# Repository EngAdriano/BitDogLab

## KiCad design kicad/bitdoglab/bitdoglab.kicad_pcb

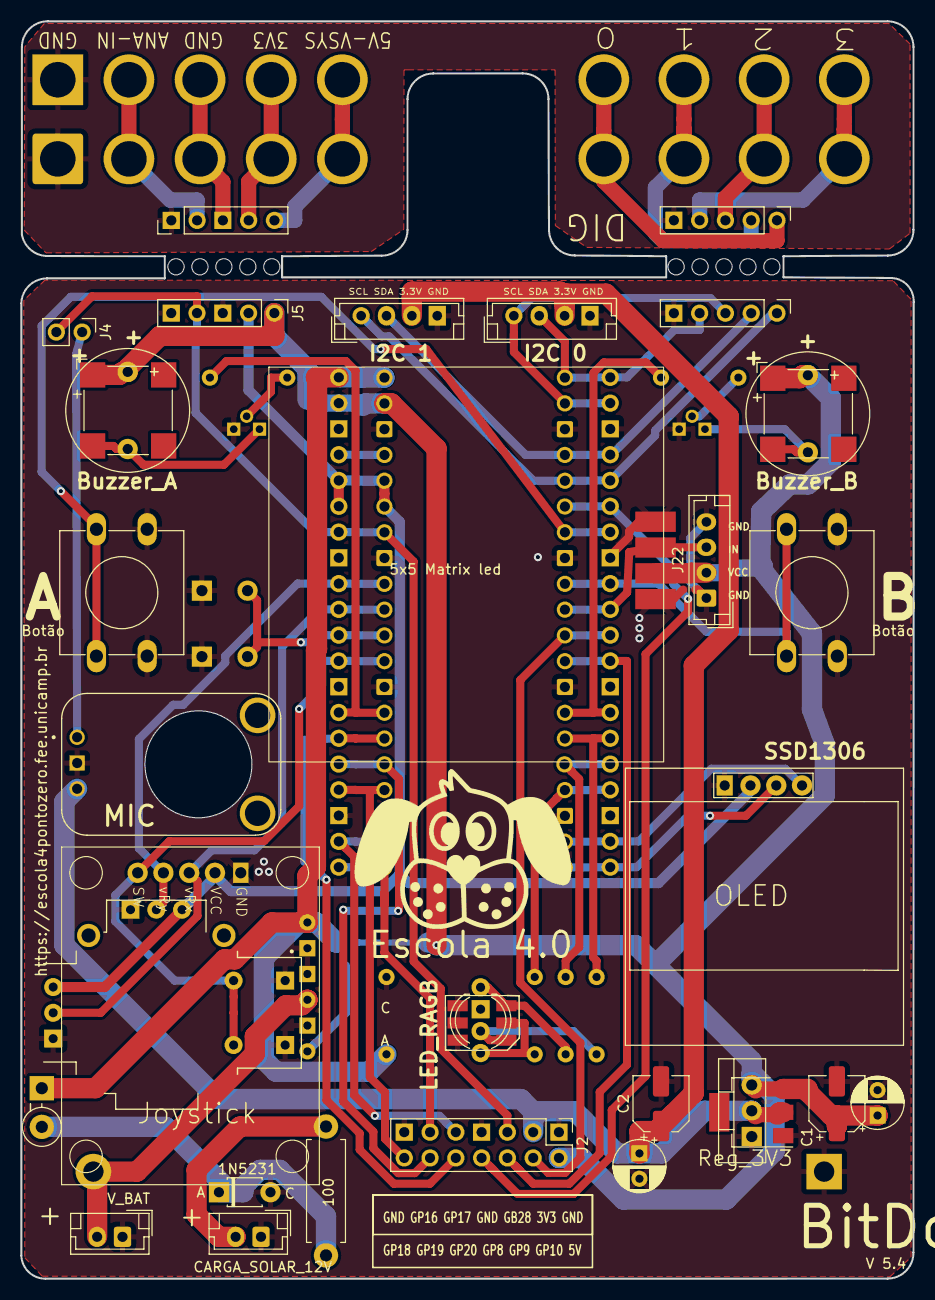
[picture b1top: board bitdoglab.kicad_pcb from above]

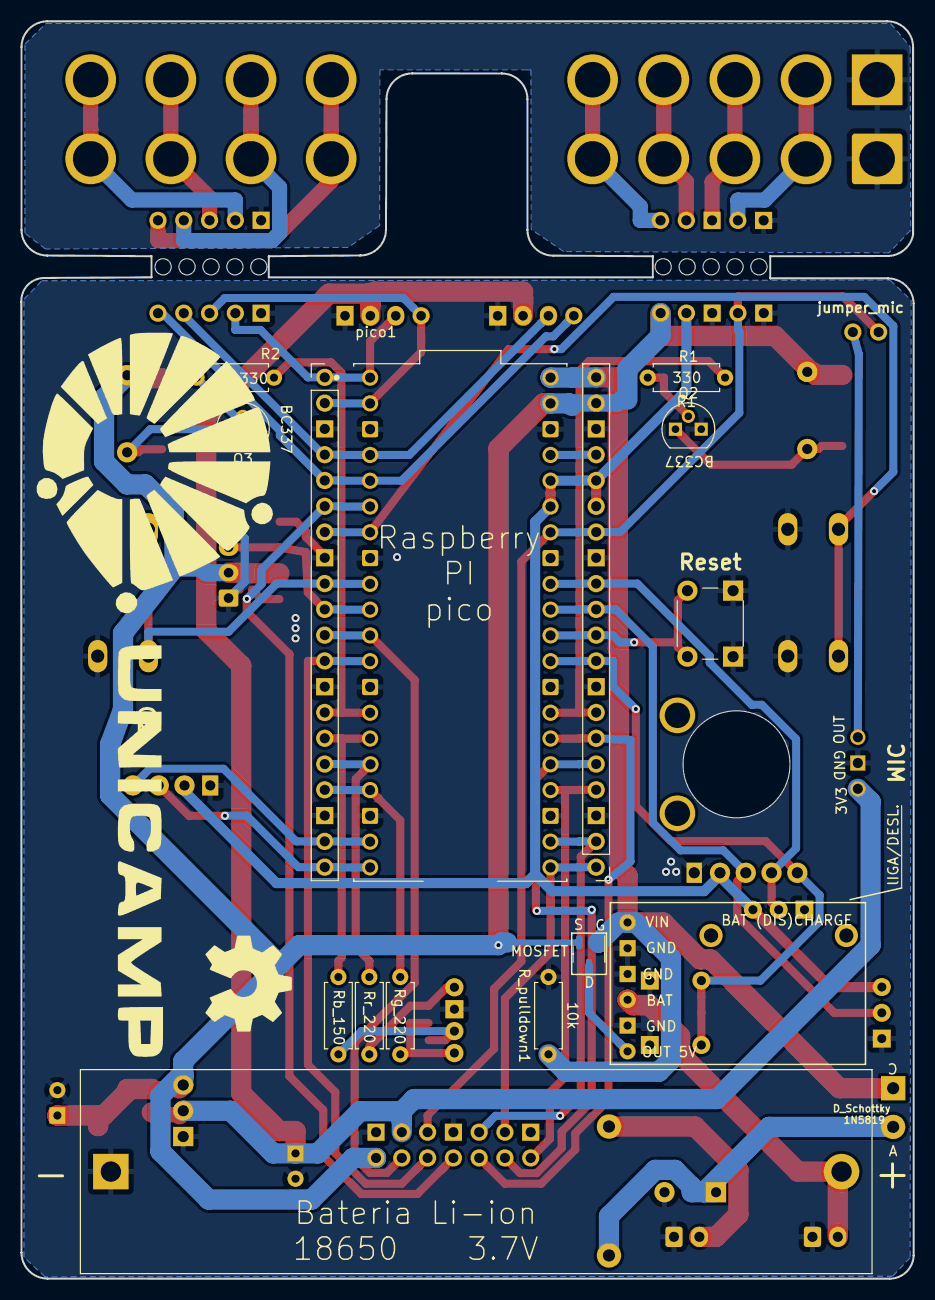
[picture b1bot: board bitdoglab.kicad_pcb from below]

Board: 2 copper layers, 87.9 x 123.9 mm, 60 parts (17 on the bottom side), 54 nets.

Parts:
BT1: Battery_Cell; BatteryHolder_MPD_BH-18650-PC2
BZ1: Buzzer_A; Buzzer_12x9.5RM7.6
BZ2: Buzzer_A_SMD; MagneticBuzzer_CUI_CMT-8504-100-SMT
BZ3: Buzzer_B; Buzzer_12x9.5RM7.6
BZ4: Buzzer_B_SMD; MagneticBuzzer_CUI_CMT-8504-100-SMT
C1, C2: C_smd; CP_Elec_5x5.9
C3, C4: C_pth; CP_Radial_D5.0mm_P2.50mm
CARGA_SOLAR1: CARGA_SOLAR_12V; JST_EH_B2B-EH-A_1x02_P2.50mm_Vertical
Charge_DisCharge1: BAT (DIS)CHARGE; Charger2A
D1: LED_RGB_SMD; LED_RGB_5050-6
D2: LED_RAGB; LED_D5.0mm-4_RGB_Wide_Pins
D3: 1N5231; D_T-1_P5.08mm_Horizontal
D4: D_Schottky; D_DO-15_P3.81mm_Vertical_KathodeUp
G1: LOGO; logo bitDog 25mm
G2: LOGO; unicamp V2A
G3: LOGO
J1, J3: Conn_01x20_Socket; PinHeader_1x20_P2.54mm_Vertical
J2: conector_idc; PinHeader_2x07_P2.54mm_Vertical
J4: jumper_mic; PinHeader_1x02_P2.54mm_Vertical
J5, J6, J12, J13: Conn_01x05_Pin; PinHeader_1x05_P2.54mm_Vertical
J7, J9: GND; SolderWire-2sqmm_1x02_P7.8mm_D2mm_OD3.9mm
J8: ANA-IN; SolderWire-2sqmm_1x02_P7.8mm_D2mm_OD3.9mm
J10: 3V3; SolderWire-2sqmm_1x02_P7.8mm_D2mm_OD3.9mm
J11: 5V-VSYS; SolderWire-2sqmm_1x02_P7.8mm_D2mm_OD3.9mm
J14: 5x5 Matrix led; Ws2812_led_5050_rgb_5x5
J15: 0; SolderWire-2sqmm_1x02_P7.8mm_D2mm_OD3.9mm
J16: 1; SolderWire-2sqmm_1x02_P7.8mm_D2mm_OD3.9mm
J17: 2; SolderWire-2sqmm_1x02_P7.8mm_D2mm_OD3.9mm
J18: 3; SolderWire-2sqmm_1x02_P7.8mm_D2mm_OD3.9mm
J19: JOYSTICK; ky-023
J20, J21, J22: Conn_01x04_Pin; JST_EH_B4B-EH-A_1x04_P2.50mm_Vertical
JOY1: JOYSTICK; XDCR_COM-09032
OLED1: SSD1306; 128x64OLED
Q1: DMG2305UX-13; SOT-23-3
Q2, Q3: BC337; TO-92
R1, R2: 330; R_Axial_DIN0207_L6.3mm_D2.5mm_P7.62mm_Horizontal
R_1W1: 100; R_Axial_DIN0411_L9.9mm_D3.6mm_P12.70mm_Horizontal
R_pulldown1: 10k; R_Axial_DIN0207_L6.3mm_D2.5mm_P7.62mm_Horizontal
Rb_150: 150; R_Axial_DIN0207_L6.3mm_D2.5mm_P7.62mm_Horizontal
Reg_3V3: 3.3v_smd; SOT-223
Rg_220: 220; R_Axial_DIN0207_L6.3mm_D2.5mm_P7.62mm_Horizontal
Rr_220: 220; R_Axial_DIN0207_L6.3mm_D2.5mm_P7.62mm_Horizontal
SW1: Reset; SW_PUSH_6mm
SW2, SW3: Botão; SW_PUSH-12mm
U1: 3.3v_tht; TO-220-3_Vertical
U4: MIC; MODULE_1063
V_BAT1: V_BAT; JST_EH_B2B-EH-A_1x02_P2.50mm_Vertical
pico1: SC0918; MODULE_SC0918

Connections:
3.3_OUT: J3.15, J3.16, J5.2, J19.2, JOY1.H1, JOY1.V1, OLED1.2 (VCC), pico1.35 (ADC_VREF), pico1.36 (3V3_OUT)
3.3_OUT_EXT: J6.4, J10.1, J10.2
+3.3V: C2.1, C4.1, J2.3, J20.3, J21.3, Reg_3V3.2 (VO), U1.2, U4.3 (VCC)
/AGND_EXT: J6.3, J9.1, J9.2
/GND_EXT: J6.1, J7.1, J7.2, J13.5
/GP0: J1.1, J12.4, J21.2, pico1.1 (GP0)
/GP0_EXT: J13.4, J18.1, J18.2
/GP01: J1.2, J12.3, J21.1, pico1.2 (GP1)
/GP01_EXT: J13.3, J17.1, J17.2
/GP02: J1.4, J12.2, J20.2, pico1.4 (GP2)
/GP02_EXT: J13.2, J16.1, J16.2
/GP03: J1.5, J12.1, J20.1, pico1.5 (GP3)
/GP03_EXT: J13.1, J15.1, J15.2
/GP04: J1.6, J2.8, pico1.6 (GP4)
/GP08: J1.11, J2.4, pico1.11 (GP8)
/GP09: J1.12, J2.6, pico1.12 (GP9)
/GP10: J1.14, R2.1, pico1.14 (GP10)
/GP11: J1.15, Rb_150.2, pico1.15 (GP11)
/GP12: J1.16, Rr_220.2, pico1.16 (GP12)
/GP13: J1.17, Rg_220.2, pico1.17 (GP13)
/GP16: J2.11, J3.1, pico1.21 (GP16)
/GP17: J2.9, J3.2, pico1.22 (GP17)
/GP18: J2.14, J3.4, pico1.24 (GP18)
/GP19: J2.12, J3.5, pico1.25 (GP19)
/GP20: J2.10, J3.6, pico1.26 (GP20)
/GP28: J2.5, J3.14, J4.2, J5.4, pico1.34 (GP28)
/GP28_EXT: J6.2, J8.1, J8.2
/in: J1.10, J14.2, J22.3, pico1.10 (GP7)
/pino_07: J1.7, SW2.1, pico1.7 (GP5)
/pino_09: J1.9, SW3.1, pico1.9 (GP6)
/pino_19: J1.19, OLED1.4 (SDA), pico1.19 (GP14)
/pino_20: J1.20, OLED1.3 (SCL), pico1.20 (GP15)
/pino_27: J3.7, R1.1, pico1.27 (GP21)
/pino_29: J3.9, J19.5, JOY1.B2A, JOY1.B2B, pico1.29 (GP22)
/pino_30: J3.10, SW1.1, pico1.30 (RUN)
/pino_31: J3.11, J19.3, JOY1.H2, pico1.31 (GP26)
/pino_32: J3.12, J19.4, JOY1.V2, pico1.32 (GP27)
/pino_37: J3.17, pico1.37 (3V3_EN)
GNDREF: BT1.2 (-), C1.2, C2.2, C3.2, C4.2, CARGA_SOLAR1.1, Charge_DisCharge1.2 (GND), Charge_DisCharge1.4 (GND), Charge_DisCharge1.5 (GND), D1.1 (RK), D1.2 (GK), D1.3 (BK), D2.2 (K), D3.2 (A), J1.3, J1.8, J1.13, J1.18, J2.1, J2.7, J2.13, J3.3, J3.8, J3.13, J3.18, J5.3, J5.5, J12.5, J14.1, J14.4, J19.1, J20.4, J21.4, J22.1, J22.4, JOY1.B1A, JOY1.B1B, JOY1.H3, JOY1.V3, OLED1.1 (GND), Q2.3 (E), Q3.3 (E), R_pulldown1.2, Reg_3V3.1 (ADJ), SW1.2, SW2.2, SW3.2, U1.1, U4.2 (GND), V_BAT1.1, pico1.3 (GND), pico1.8 (GND), pico1.13 (GND), pico1.18 (GND), pico1.23 (GND), pico1.28 (GND), pico1.33 (AGND), pico1.38 (GND)
unnamed: BZ1.2 (+), BZ2.2 (+), Q2.1 (C)
unnamed: BZ3.2 (+), BZ4.2 (+), Q3.1 (C)
unnamed: CARGA_SOLAR1.2, R_1W1.2
unnamed: Charge_DisCharge1.1 (OUT5V), Q1.3 (D)
unnamed: D1.4 (BA), D2.3 (BA), Rb_150.1
unnamed: D1.5 (GA), D2.4 (GA), Rg_220.1
unnamed: D1.6 (RA), D2.1 (RA), Rr_220.1
unnamed: D3.1 (K), D4.2 (A), R_1W1.1
unnamed: J4.1, U4.1 (OUT)
unnamed: Q2.2 (B), R1.2
unnamed: Q3.2 (B), R2.2
VBUS: Charge_DisCharge1.6 (VIN), D4.1 (K), J3.20, Q1.1 (G), R_pulldown1.1, pico1.40 (VBUS)
VSYS: BZ1.1 (-), BZ2.1 (-), BZ3.1 (-), BZ4.1 (-), C1.1, C3.1, J2.2, J3.19, J5.1, J14.3, J22.2, Q1.2 (S), Reg_3V3.3 (VI), U1.3, pico1.39 (VSYS)
VSYS_EXT: J6.5, J11.1, J11.2
V_BAT +: BT1.1 (+), Charge_DisCharge1.3 (BAT), V_BAT1.2

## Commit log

2025-02-01 atualizar
2025-06-05 Atualização
